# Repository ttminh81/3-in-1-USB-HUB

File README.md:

# 3-in-1-USB-HUB
A usb hub design with RJ port and SD card

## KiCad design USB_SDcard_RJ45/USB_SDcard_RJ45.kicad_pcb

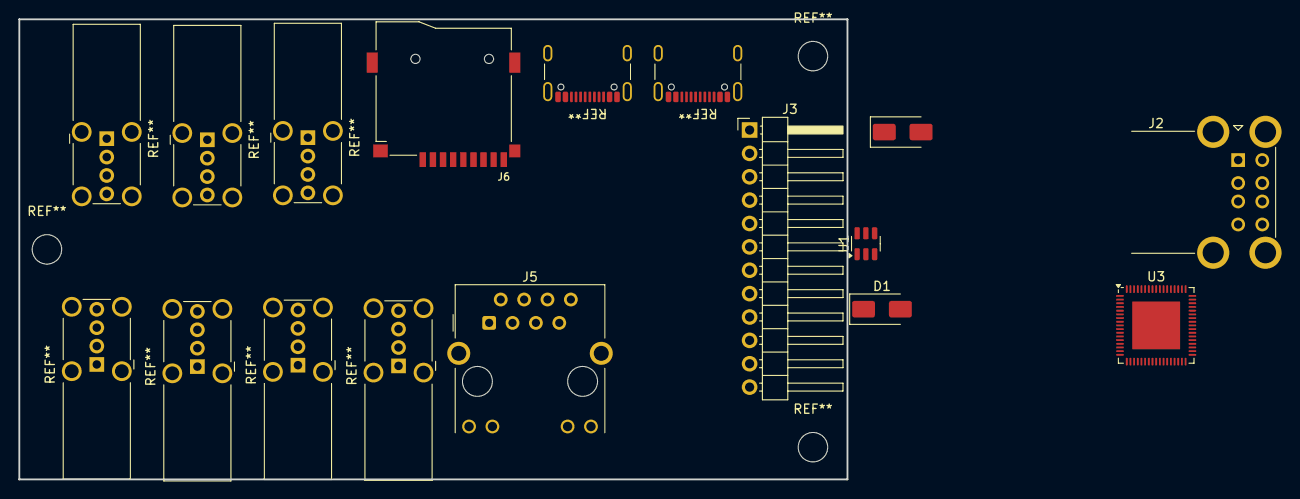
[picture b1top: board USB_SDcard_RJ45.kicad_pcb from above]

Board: 2 copper layers, 90.0 x 50.0 mm, 8 parts (0 on the bottom side), 10 nets, no tracks yet.

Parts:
D1, D2: SS34; D_SMA
J2: USB_A_Stacked; USB_A_CUI_UJ2-ADH-TH_Horizontal_Stacked
J3: Conn_01x12_Pin; PinHeader_1x12_P2.54mm_Horizontal
J5: RJ45_Hanrun_HR911105A_Horizontal
J6: Micro_SD_Card_Det1; MiSD-PP-9P-V2
U1: CH217K; SOT-23-6
U3: CH339W; QFN-68-1EP_8x8mm_P0.4mm_EP5.2x5.2mm

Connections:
+3.3V: J3.10, J6.4 (VDD)
+5V: D1.1 (K), D2.1 (K), J3.12, U1.6 (VIN)
/LED_ACT: J5.10, U3.31 (LED_ACT/CFG0)
/LED_LINK: J5.11, U3.35 (LED_LINK/CFG1)
/SD_D0: J6.7 (DAT0), U3.51 (SD_D0)
/SD_D1: J6.8 (DAT1), U3.50 (SD_D1)
/SD_D2: J6.1 (DAT2), U3.49 (SD_D2)
/SD_D3: J6.2 (DAT3/CD), U3.48 (SD_D3)
GND: J2.4 (GND1), J2.8 (GND2), J2.9 (Shield), J3.9, J3.11, J5.8, J6.6 (VSS), J6.10 (SHIELD), U1.2 (GND), U3.6 (GND), U3.22 (GND), U3.53 (GND), U3.61 (GND), U3.69 (GND)
VBUS: J2.1 (VBUS1), J2.5 (VBUS2), U1.1 (VOUT)

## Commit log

2025-10-07 Add kicad file and local library
2025-10-07 Add project library
2025-10-07 Add CH339F symbol
2025-10-07 Add USB stack and rj45 port
2025-10-08 Add components to schematic
2025-10-16 Add CH339 datasheet
2025-10-17 Change to CH339W hub ic
2025-10-17 Change layout to match CH339W
2025-10-17 Change USB type
